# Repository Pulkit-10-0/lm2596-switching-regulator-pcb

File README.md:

# LM2596 Switching Regulator PCB ⚡

A learning-oriented PCB design of an LM2596 adjustable buck converter created while exploring switching regulator topology and KiCad PCB workflows.

---

##  Preview

### Schematic

### PCB Layout

### 3D View (Front)

### 3D View (Back)

---

##  Features

- LM2596S-ADJ switching regulator topology
- Schottky diode based rectification (1N5821)
- Inductor-based energy storage
- Designed and routed using KiCad
- Ground-plane based layout approach

---

##  Project Structure

hardware/
├── x.kicad_sch
├── x.kicad_pcb
└── x.kicad_pro

Images/
├── pcb.png
├── pcb_3d_fv.png
└── pcb_3d_bv.png

---

##  Learning Goals

This project focuses on:

- Understanding buck converter architecture
- Switching power supply layout considerations
- High-current routing basics
- KiCad schematic and PCB workflow

---

## 🛠️ Tools Used

- KiCad (Schematic + PCB Layout)
- 3D Viewer for visualization

---

##  Future Improvements

- Add feedback resistor network calculations
- Optimize switching loop placement
- Improve power trace width analysis

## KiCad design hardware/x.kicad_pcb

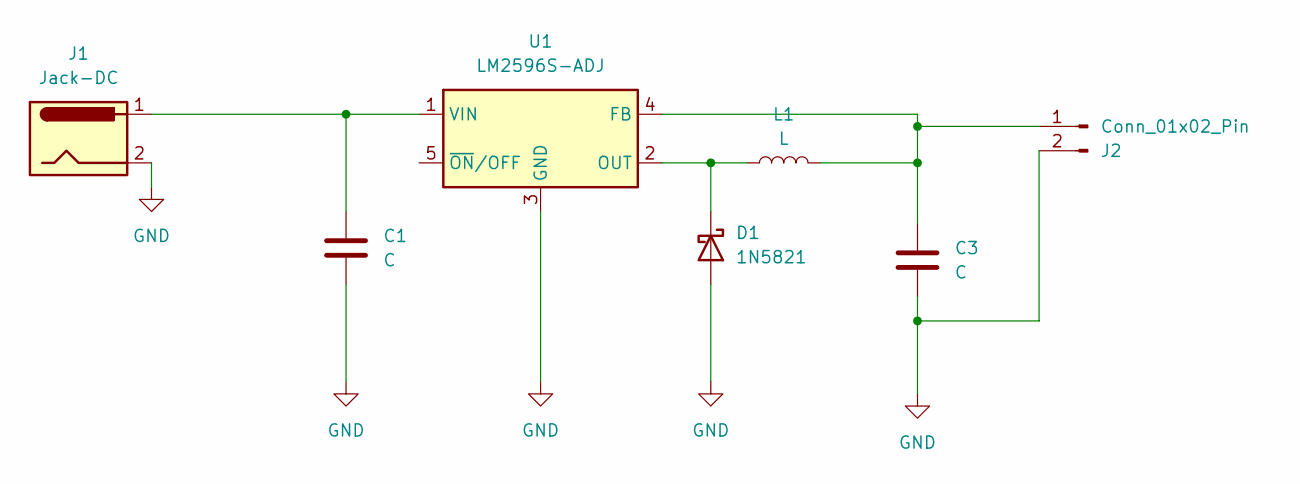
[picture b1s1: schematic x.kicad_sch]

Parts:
C1, C3: C; C_0201_0603Metric
D1: 1N5821; D_DO-201AD_P15.24mm_Horizontal
J1: Jack-DC; BarrelJack_SwitchcraftConxall_RAPC10U_Horizontal
J2: Conn_01x02_Pin; JWT_A3963_1x02_P3.96mm_Vertical
L1: L; L_6.3x6.3_H3
U1: LM2596S-ADJ; TO-263-5_TabPin3

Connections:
GND: C1.2, C3.2, D1.2 (A), J1.2, J2.2, U1.3 (GND)
unnamed: D1.1 (K), L1.1, U1.2 (OUT)
unnamed: C3.1, J2.1, L1.2, U1.4 (FB)
unnamed: C1.1, J1.1, U1.1 (VIN)

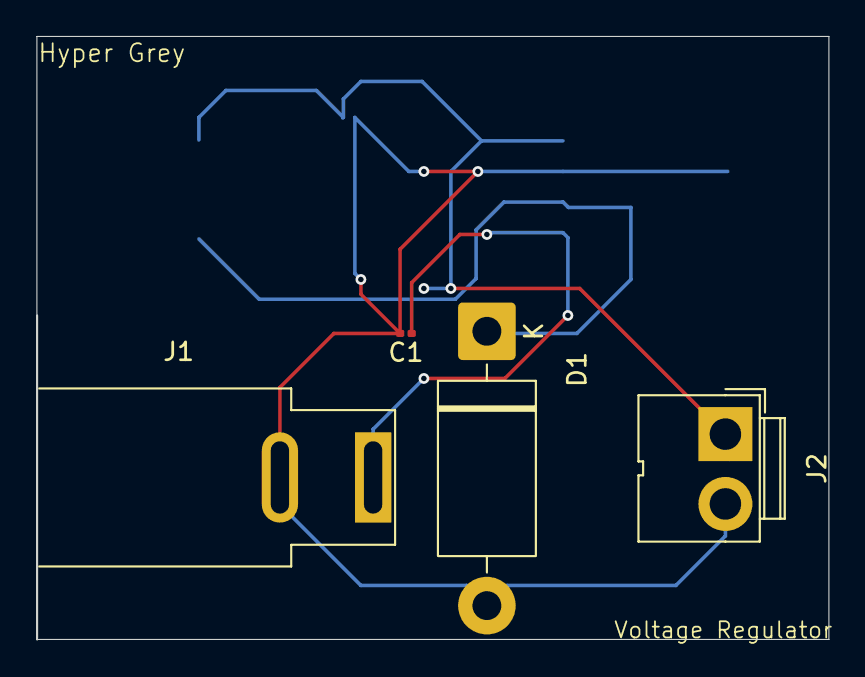
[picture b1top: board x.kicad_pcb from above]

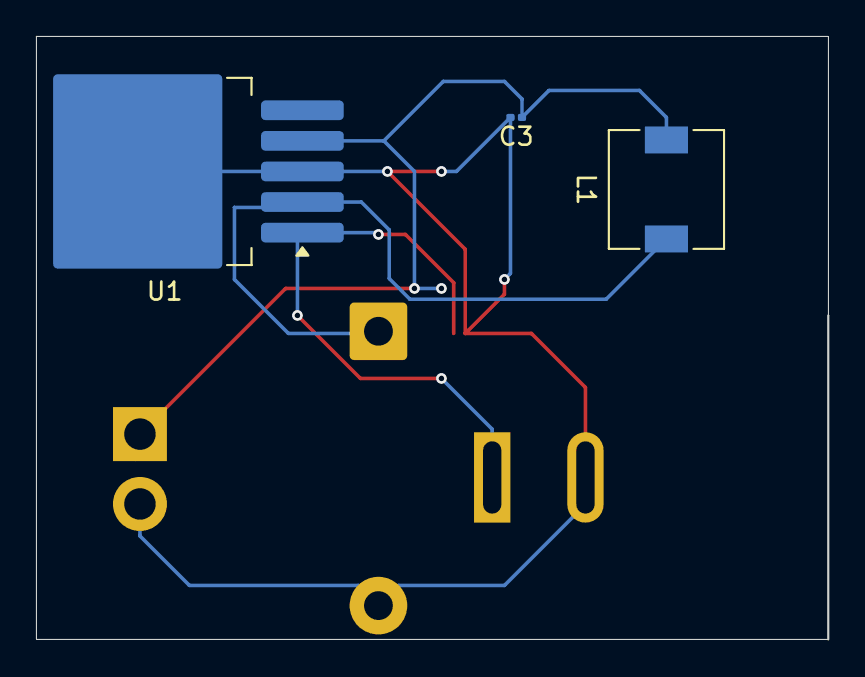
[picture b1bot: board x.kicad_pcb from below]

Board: 2 copper layers, 44.0 x 33.5 mm, 7 parts (3 on the bottom side), 4 nets.

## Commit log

2026-02-18 Initial commit: LM2596 switching regulator PCB
2026-02-18 Add schematic image to README
2026-02-18 Add README for LM2596 Switching Regulator PCB
    Added detailed project information for LM2596 Switching Regulator PCB, including features, project structure, learning goals, tools used, and future improvements.
